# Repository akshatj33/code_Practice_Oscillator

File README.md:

# code_Practice_Oscillator
This is the schematic and board layout for Code practice oscillator.

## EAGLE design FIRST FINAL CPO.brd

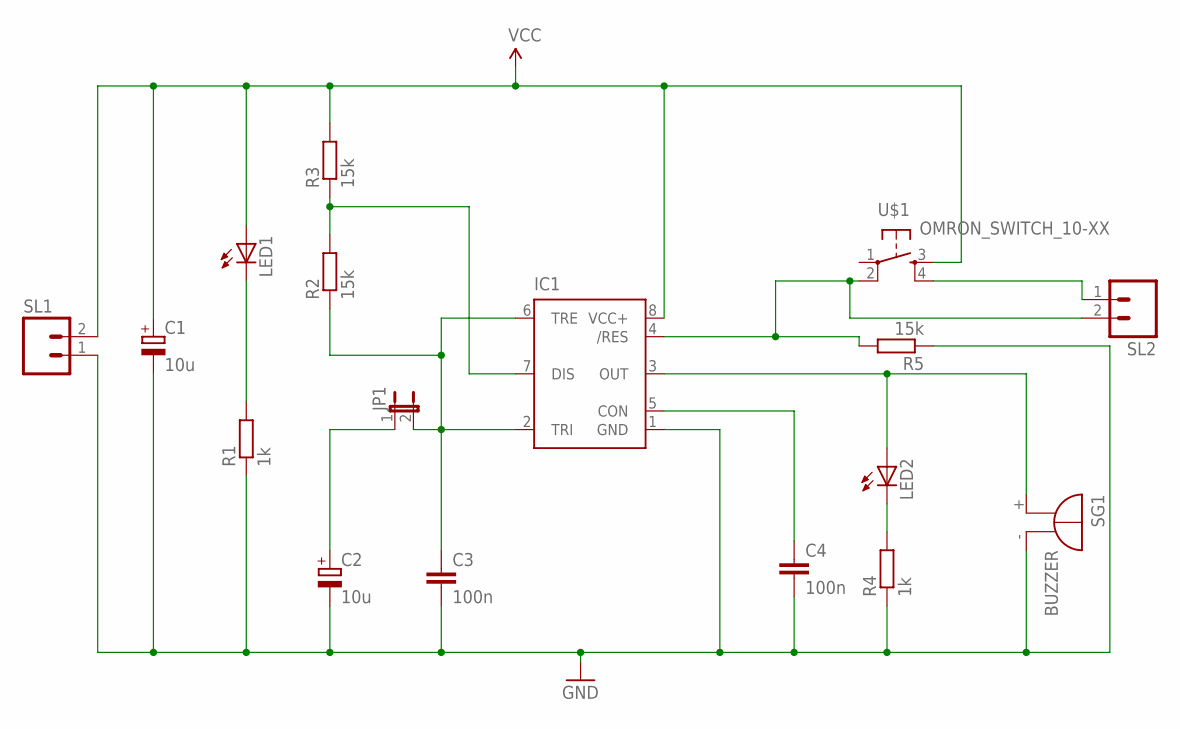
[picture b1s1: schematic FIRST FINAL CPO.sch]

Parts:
C1, C2: 10u; E2,5-5
C3, C4: 100n; C025-025X050
IC1: NE555P; DIL-08
JP1: JP1E; JP1
LED1, LED2: LED5MM
R1, R4: 1k; 0207/7
R2, R3, R5: 15k; 0207/7
SG1: BUZZER; F/TMB
SL1, SL2: M02; 02P
U$1: OMRON_SWITCH_10-XX; B3F-10XX

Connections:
GND: C1.-, C2.-, C3.2, C4.2, IC1.1 (GND), R1.1, R4.1, R5.1, SG1.-, SL1.1
unnamed: LED1.K (C), R1.2
unnamed: C2.+, JP1.1
unnamed: C3.1, IC1.2 (TRI), IC1.6 (TRE), JP1.2, R2.1
unnamed: IC1.3 (OUT), LED2.A, SG1.+
unnamed: LED2.K (C), R4.2
unnamed: IC1.7 (DIS), R2.2, R3.1
unnamed: IC1.4 (/RES), R5.2, SL2.2, U$1.2 (P1)
unnamed: SL2.1, U$1.4 (S1)
unnamed: C4.1, IC1.5 (CON)
VCC: C1.+, IC1.8 (VCC+), LED1.A, R3.2, SL1.2, U$1.3 (S)

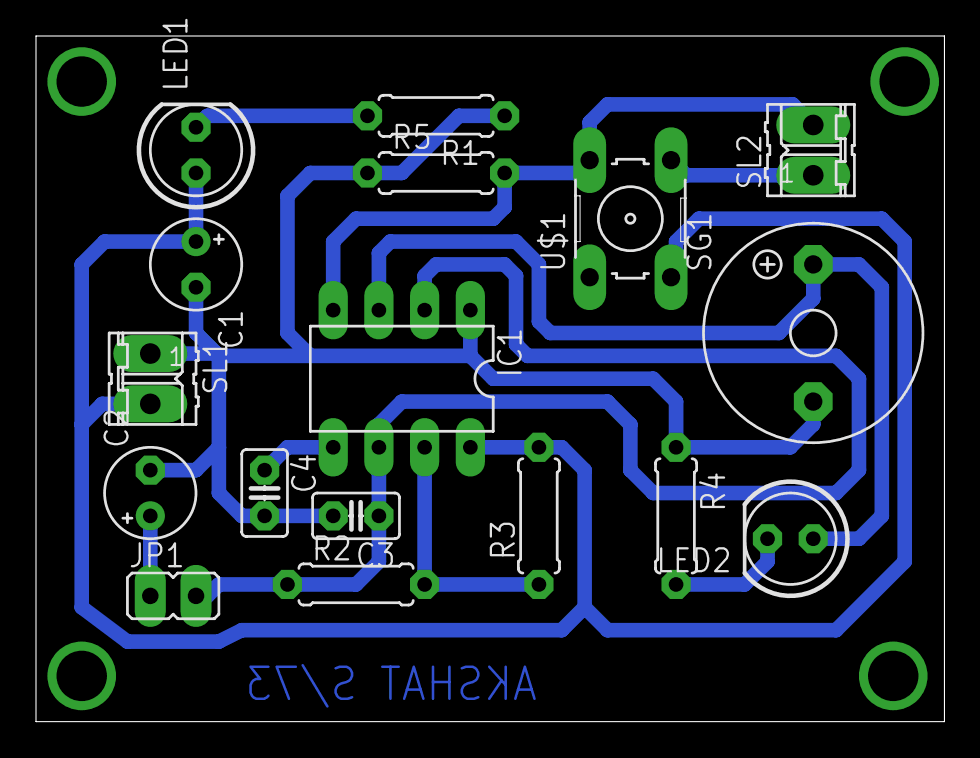
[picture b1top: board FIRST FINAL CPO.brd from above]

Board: 2 copper layers, 50.5 x 38.1 mm, 17 parts (0 on the bottom side), 11 nets.

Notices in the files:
parts and their libraries:
SparkFun-AnalogIC: Licensing:Creative Commons ShareAlike 4.0 International - https://creativecommons.org/licenses/by-sa/4.0
